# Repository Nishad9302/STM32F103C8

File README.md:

# STM32F103C8
Schematic : 
PCB Layout : 

<p>Fig.: PCB Bottom Layer</p>

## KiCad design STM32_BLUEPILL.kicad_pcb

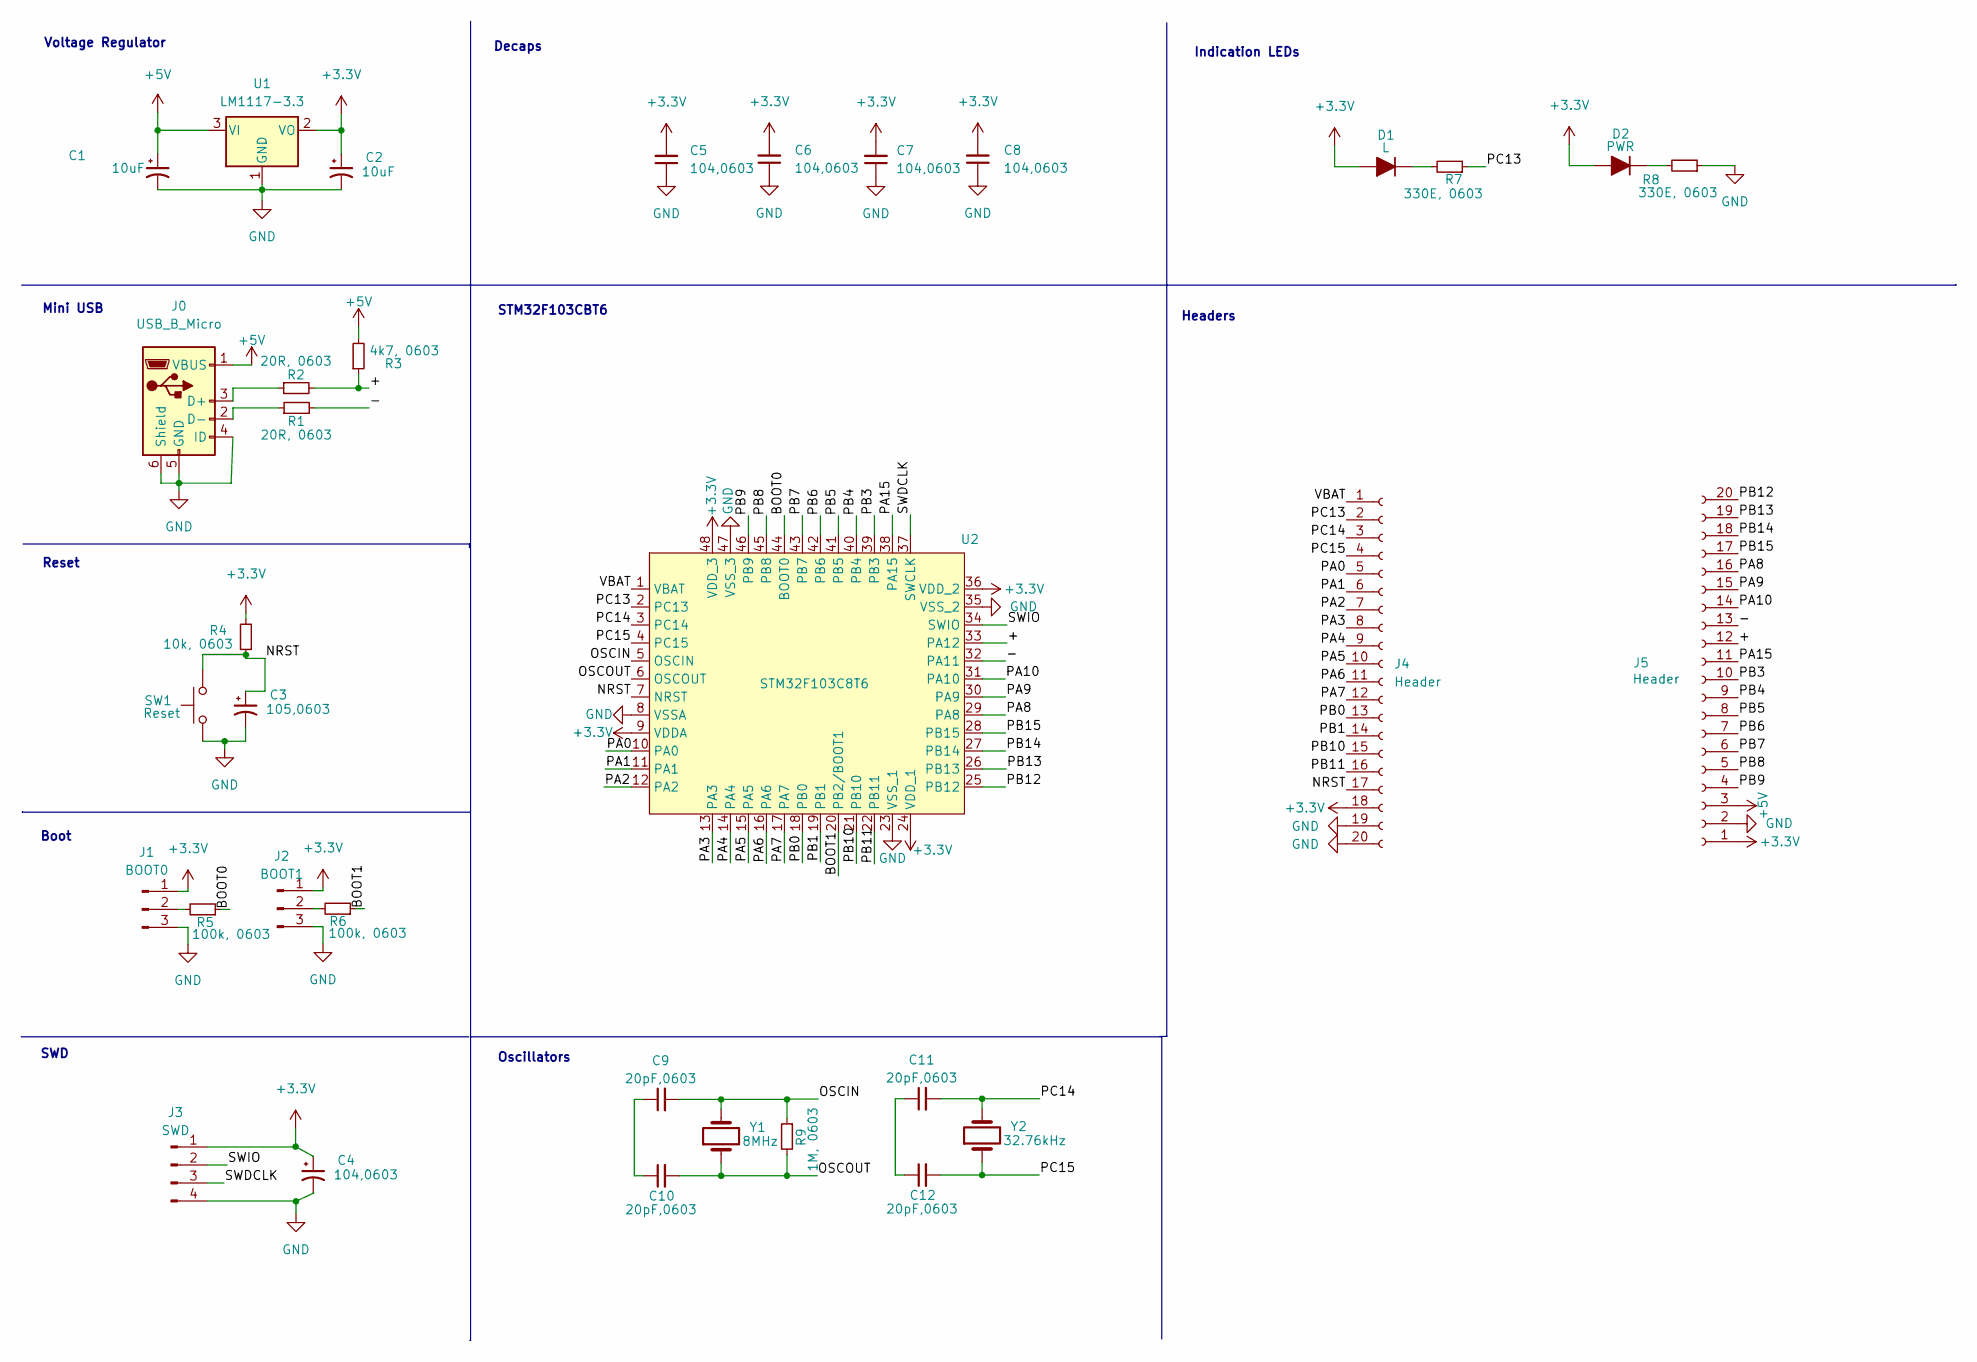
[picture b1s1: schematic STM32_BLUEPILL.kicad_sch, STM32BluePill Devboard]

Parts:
C1, C2: 10uF; CP_EIA-3216-18_Kemet-A
C3: 105,0603; C_0603_1608Metric_Pad1.08x0.95mm_HandSolder
C4, C5, C6, C7, C8: 104,0603; C_0603_1608Metric_Pad1.08x0.95mm_HandSolder
C9, C10, C11, C12: 20pF,0603; C_0603_1608Metric_Pad1.08x0.95mm_HandSolder
D1: L; LED_0805_2012Metric_Pad1.15x1.40mm_HandSolder
D2: PWR; LED_0805_2012Metric_Pad1.15x1.40mm_HandSolder
J0: USB_B_Micro; USB_Micro-B_Molex-105017-0001
J1: BOOT0; PinHeader_1x03_P2.54mm_Vertical
J2: BOOT1; PinHeader_1x03_P2.54mm_Vertical
J3: SWD; PinHeader_1x04_P2.54mm_Vertical
J4, J5: Header; PinHeader_1x20_P2.54mm_Vertical
R1, R2: 20R, 0603; R_0201_0603Metric_Pad0.64x0.40mm_HandSolder
R3: 4k7, 0603; R_0201_0603Metric_Pad0.64x0.40mm_HandSolder
R4: 10k, 0603; R_0201_0603Metric_Pad0.64x0.40mm_HandSolder
R5, R6: 100k, 0603; R_0201_0603Metric_Pad0.64x0.40mm_HandSolder
R7, R8: 330E, 0603; R_0201_0603Metric_Pad0.64x0.40mm_HandSolder
R9: 1M, 0603; R_0201_0603Metric_Pad0.64x0.40mm_HandSolder
SW1: Reset; SW_Tactile_SPST_NO_Straight_CK_PTS636Sx25SMTRLFS
U1: LM1117-3.3; SOT-23
U2: STM32F103C8T6; LQFP48_STM
Y1: 8MHz; Crystal_SMD_Abracon_ABM3-2Pin_5.0x3.2mm_HandSoldering
Y2: 32.76kHz; Crystal_SMD_MicroCrystal_CC8V-T1A-2Pin_2.0x1.2mm_HandSolder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

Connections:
+3.3V: C2.1, C4.1, C5.2, C6.2, C7.2, C8.2, D1.2 (A), D2.2 (A), J1.1, J2.1, J3.1, J4.18, J5.1, R4.2, U1.2 (VO), U2.9 (VDDA), U2.24 (VDD_1), U2.36 (VDD_2), U2.48 (VDD_3); also elsewhere on the board
+5V: C1.1, J0.1 (VBUS), J5.3, R3.2, U1.3 (VI)
/+: J5.12, R2.2, R3.1, U2.33 (PA12)
/-: J5.13, R1.2, U2.32 (PA11)
/BOOT0: R5.1, U2.44 (BOOT0)
/BOOT1: R6.1, U2.20 (PB2/BOOT1)
/NRST: C3.1, J4.17, R4.1, SW1.2, U2.7 (NRST)
/OSCIN: C9.2, R9.1, U2.5 (OSCIN), Y1.2
/OSCOUT: C10.2, R9.2, U2.6 (OSCOUT), Y1.1
/PA0: J4.5, U2.10 (PA0)
/PA1: J4.6, U2.11 (PA1)
/PA2: J4.7, U2.12 (PA2)
/PA3: J4.8, U2.13 (PA3)
/PA4: J4.9, U2.14 (PA4)
/PA5: J4.10, U2.15 (PA5)
/PA6: J4.11, U2.16 (PA6)
/PA7: J4.12, U2.17 (PA7)
/PA8: J5.16, U2.29 (PA8)
/PA9: J5.15, U2.30 (PA9)
/PA10: J5.14, U2.31 (PA10)
/PA15: J5.11, U2.38 (PA15)
/PB0: J4.13, U2.18 (PB0)
/PB1: J4.14, U2.19 (PB1)
/PB3: J5.10, U2.39 (PB3)
/PB4: J5.9, U2.40 (PB4)
/PB5: J5.8, U2.41 (PB5)
/PB6: J5.7, U2.42 (PB6)
/PB7: J5.6, U2.43 (PB7)
/PB8: J5.5, U2.45 (PB8)
/PB9: J5.4, U2.46 (PB9)
/PB10: J4.15, U2.21 (PB10)
/PB11: J4.16, U2.22 (PB11)
/PB12: J5.20, U2.25 (PB12)
/PB13: J5.19, U2.26 (PB13)
/PB14: J5.18, U2.27 (PB14)
/PB15: J5.17, U2.28 (PB15)
/PC13: J4.2, R7.1, U2.2 (PC13)
/PC14: C11.2, J4.3, U2.3 (PC14), Y2.2
/PC15: C12.2, J4.4, U2.4 (PC15), Y2.1
/SWDCLK: J3.3, U2.37 (SWCLK)
/SWIO: J3.2, U2.34 (SWIO)
/VBAT: J4.1, U2.1 (VBAT)
GND: C1.2, C2.2, C3.2, C4.2, C5.1, C6.1, C7.1, C8.1, J0.4 (ID), J0.5 (GND), J0.6 (Shield), J1.3, J2.3, J3.4, J4.19, J4.20, J5.2, R8.1, SW1.1, U1.1 (GND), U2.8 (VSSA), U2.23 (VSS_1), U2.35 (VSS_2), U2.47 (VSS_3)
unnamed: C9.1, C10.1
unnamed: C11.1, C12.1
unnamed 45: D1.1 (K), R7.2; also elsewhere on the board
unnamed 46: D2.1 (K), R8.2; also elsewhere on the board
unnamed: J0.3 (D+), R2.1
unnamed: J0.2 (D-), R1.1
unnamed: J1.2, R5.2
unnamed: J2.2, R6.2

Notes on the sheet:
Oscillators
SWD
Boot
Mini USB
Indication LEDs
STM32F103CBT6
Headers
Voltage Regulator
Reset
Decaps

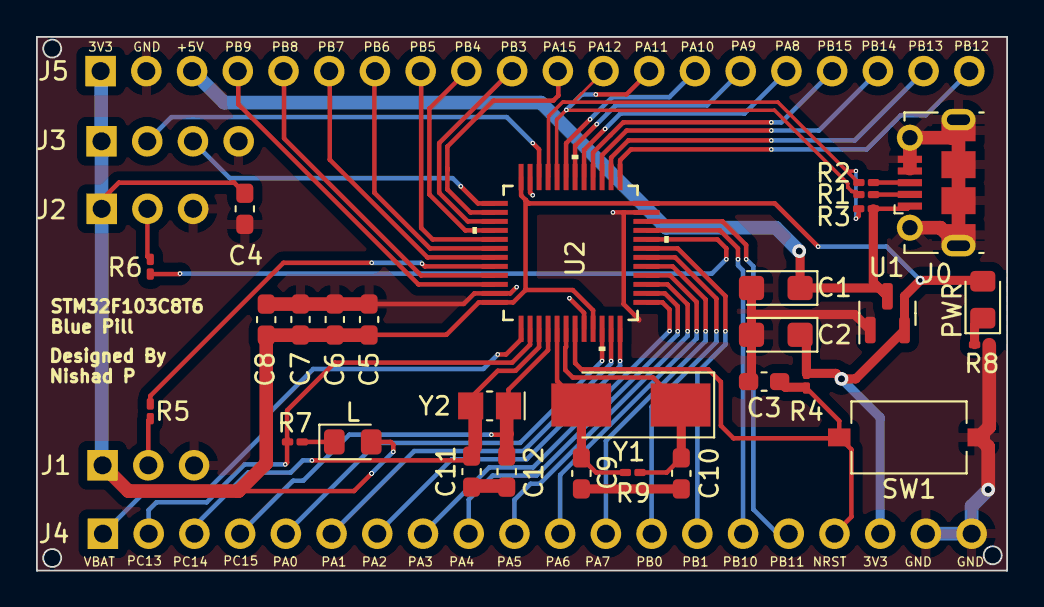
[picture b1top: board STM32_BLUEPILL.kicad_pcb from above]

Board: 2 copper layers, 53.9 x 29.6 mm, 34 parts (0 on the bottom side), 51 nets.

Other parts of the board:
L: L; LED_0805_2012Metric_Pad1.15x1.40mm_HandSolder
PWR: PWR; LED_0805_2012Metric_Pad1.15x1.40mm_HandSolder

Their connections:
+3.3V: L.2 (A), PWR.2 (A); also elsewhere on the board
unnamed 45: L.1 (K); also elsewhere on the board
unnamed 46: PWR.1 (K); also elsewhere on the board
